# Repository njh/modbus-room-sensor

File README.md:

AL100 Modbus Room Sensor
========================

A temperature and humidity room sensor board for building automation. It is a Modbus RTU
server on RS-485, runs from 5–24 V DC, and fits in a standard wall-mounted room
sensor enclosure.

It uses a I²C sensor on a separate 19x19mm board, which is compatible with some of the
[Pimoroni Breakout Sensor Boards], so it is possible to use alternative sensors with it.

It is open source hardware and software: the KiCad design files, schematics,
Gerbers, bootloader and documentation are all MIT licensed, so you can build and
modify your own.

The board is Arduino compatible: it is designed to be very similar to the 3.3 V
[Arduino Pro Mini], so it can be programmed with the same settings.

Features
--------

- Sensirion [SHT4x] temperature and humidity sensor, on a swappable plug-in module
- Modbus RTU over half-duplex RS-485, with a ±70 V fault-protected transceiver
- Unit ID from 1 to 15, set with jumpers
- Jumper to enable the 120 Ω bus terminator
- 5–24 V DC supply, with a resettable fuse, reverse-polarity and surge protection
- Power and RS-485 on one 4-way HT396 connector, with the same pinout as M5Stack's [PWR485]
- Spare I²C socket for adding another sensor
- Fits the [Camdenboss CBRS01VWH] "Size 1" vented room sensor enclosure
- Designed in [KiCad], and assembled by JLCPCB

Downloads
---------

Schematics and Gerber files are built by GitHub Actions on every push to `main`,
and published as a [GitHub release][latest release]. These links always point to
the latest release:

| File                                       | Description                              |
|--------------------------------------------|------------------------------------------|
| [modbus-room-sensor-schematic.pdf]         | Main board schematic                     |
| [modbus-room-sensor-gerbers.zip]           | Main board Gerber and drill files        |
| [sht4x-breakout-schematic.pdf]             | SHT4x breakout board schematic           |
| [sht4x-breakout-gerbers.zip]               | SHT4x breakout board Gerber and drill files |

Specifications
--------------

| Item             | Value                                            |
|------------------|--------------------------------------------------|
| Supply voltage   | 5-24 V DC                                        |
| Interface        | RS-485, half-duplex                              |
| Protocol         | Modbus RTU, 9600 baud, 8N1                       |
| Unit ID          | 1-15, set by jumpers (default 1)                 |
| Sensor           | Sensirion SHT41: typically ±0.2 °C and ±1.8 %RH  |
| Resolution       | 0.1 °C and 0.1 %RH                               |
| Update interval  | 2 seconds                                        |
| Main board       | 73.3 x 73.3 mm, 2 layers                         |
| Enclosure        | [Camdenboss CBRS01VWH], 86 x 86 mm               |

Hardware
--------

### Main components

| Ref | Function             | Part                         |
|-----|----------------------|------------------------------|
| U1  | Microcontroller      | [ATmega328P] (3.3 V, 8 MHz)  |
| U3  | RS-485 transceiver   | [THVD2410]                   |
| U5  | 3.3 V buck converter | [AP63203]                    |
|     | Sensor               | [SHT4x], on the [SHT4x breakout board](sht4x-breakout/) |

### Connectors and jumpers

| Ref | Name         | Description |
|-----|--------------|-------------|
| J1  | Terminal     | 4-way 3.96 mm HT396 socket: `GND`, `VIN`, `A+`, `B-`. The same pinout as M5Stack's [PWR485], so it can share a 9–24 V supply and RS-485 bus with M5Stack devices |
| J2  | FTDI Serial  | 6-pin header for a 3.3 V FTDI cable, for uploading firmware and the debug console |
| J3  | ICSP         | 2x3 header for writing the bootloader |
| J4  | Sensor board | 5-way socket for the SHT4x breakout: `GND`, `INT`, `SCL`, `SDA`, `3.3V` |
| J5  | I2C          | 4-way JST PH socket: `SCL`, `SDA`, `3.3V`, `GND` (the same order as Grove and STEMMA) |
| J6  | Unit ID      | 2x4 header for the unit ID jumpers |
| JP1 | Terminate    | Fit a jumper to connect the 120 Ω terminator across A and B |

There are no I²C pull-up resistors on the main board. The SHT4x breakout has
4.7 kΩ pull-ups, so a sensor on J5 without the breakout needs its own.

Installation
------------

1. Set the unit ID by fitting jumpers on J6. The unit ID is the sum of the
   values printed next to the fitted jumpers (1, 2, 4 and 8), so fitting 1 and
   4 gives unit ID 5. With no jumpers fitted, the unit ID is 1. The jumpers are
   only read at power-up.
2. Connect the supply to `VIN` and `GND` on J1, and the RS-485 bus to `A+` and `B-`.
3. If the sensor is at one end of the bus, fit the `Terminate` jumper (JP1).
   Otherwise, leave it off.

Each device on the bus needs a unique unit ID.

Modbus Interface
----------------

The sensor board is a Modbus RTU server on RS-485 (J1), at 9600 baud, 8N1.

| Address  | Type                    | Name              | Format          | Units |
|----------|-------------------------|-------------------|-----------------|-------|
| `0x0001` | Input register (FC 04)  | Temperature       | Signed, x 10    | °C    |
| `0x0002` | Input register (FC 04)  | Relative humidity | Unsigned, x 10  | %RH   |

Addresses are the zero-based addresses sent on the bus. Tools that use
one-based 3xxxx numbering call these 30002 and 30003.

For example, `0x00EA` is 23.4 °C and `0xFFCB` is −5.3 °C. Both registers read
`0x8000` if the sensor couldn't be read.

### Reading the sensor

With a USB to RS-485 adapter, you can read the sensor using [modbus-cli]:

```sh
pip install modbus_cli
modbus -b 9600 -s 1 /dev/ttyUSB0 i@1/h i@2/H
```

Programming
-----------

The firmware is in [firmware/ModbusFirmware](firmware/ModbusFirmware). It needs
the [ModbusRTUSlave] and [Sensirion I2C SHT4x] libraries, which can be installed
with the Arduino IDE's Library Manager.

The board is programmed like a 3.3 V Arduino Pro Mini. In the Arduino IDE, choose
the **Arduino Pro or Pro Mini** board, with the **ATmega328P (3.3V, 8 MHz)**
processor option, and upload with a 3.3 V FTDI cable on J2.

A new board needs a bootloader before it can be programmed from the Arduino IDE.
See [bootloader/README.md](bootloader/README.md) for how to write it using ICSP.

Modbus doesn't work over the FTDI header, because the RS-485 receiver drives the
same RX line. Instead, at power-up the firmware prints when it was built, the unit
ID and the SHT4x serial number to the FTDI header, at 9600 baud.

ATmega328P pin mapping
----------------------

If you want to make your own software / firmware for the board, here is the
pin mapping for use in the Arduino IDE:

| Port | Arduino | Function                                |
|------|---------|-----------------------------------------|
| PD0  | D0      | UART RX, from RS-485 and FTDI           |
| PD1  | D1      | UART TX, to RS-485 and FTDI             |
| PD2  | D2      | RS-485 driver enable (DE)               |
| PD3  | D3      | RS-485 receiver enable (RE, active low) |
| PD4  | D4      | Sensor board interrupt                  |
| PD5  | D5      | _Unused_                                |
| PD6  | D6      | _Unused_                                |
| PD7  | D7      | _Unused_                                |
| PB0  | D8      | _Unused_                                |
| PB1  | D9      | _Unused_                                |
| PB2  | D10     | _Unused_                                |
| PB3  | D11     | ICSP MOSI                               |
| PB4  | D12     | ICSP MISO                               |
| PB5  | D13     | ICSP SCK and the Red LED                |
| PC0  | A0      | Unit ID jumper, value 1                 |
| PC1  | A1      | Unit ID jumper, value 2                 |
| PC2  | A2      | Unit ID jumper, value 4                 |
| PC3  | A3      | Unit ID jumper, value 8                 |
| PC4  | A4      | I²C data                                |
| PC5  | A5      | I²C clock                               |
| ADC6 | A6      | _Unused_                                |
| ADC7 | A7      | _Unused_                                |
| PC6  |         | Reset, from ICSP and FTDI auto-reset    |

Making a Board
--------------

The surface-mount parts are assembled by JLCPCB (Economic PCBA, top side only).
The LCSC part numbers are in the `LCSC` field of each part in the schematics.
In JLCPCB's placement preview, check the orientation of U1, U3, U5, D2 and D3.

The through-hole parts are fitted by hand. In soldering order:

| Ref | Part                                                    |
|-----|---------------------------------------------------------|
| J4  | 1x5 right-angle socket header, 2.54 mm                  |
| J5  | JST PH 4-way vertical socket (B4B-PH-K), optional       |
| F1  | Littelfuse RXEF050, 0.5 A resettable fuse               |
| J2  | 1x6 pin header, 2.54 mm                                 |
| J3  | 2x3 pin header, 2.54 mm                                 |
| J6  | 2x4 pin header, 2.54 mm, and jumpers                    |
| JP1 | 1x2 pin header, 2.54 mm, and a jumper                   |
| J1  | Kefa HT396R 4-way horizontal socket, 3.96 mm            |
| C1  | 47 µF 50 V electrolytic, 6.3 mm diameter, 2.5 mm pitch  |

You also need a [Camdenboss CBRS01VWH] enclosure, and 5 pan head M2.3 x 5 mm
self-tapping PCB screws.

License
-------

This project is open source hardware and software. The hardware design files,
software and documentation are all licensed under the terms of the MIT license.
See the file [LICENSE.md](LICENSE.md) for details.

[latest release]:  https://github.com/njh/modbus-room-sensor/releases/latest
[modbus-room-sensor-schematic.pdf]:  https://njh.github.io/modbus-room-sensor/modbus-room-sensor-schematic.pdf
[modbus-room-sensor-gerbers.zip]:    https://github.com/njh/modbus-room-sensor/releases/latest/download/modbus-room-sensor-gerbers.zip
[sht4x-breakout-schematic.pdf]:      https://njh.github.io/modbus-room-sensor/sht4x-breakout-schematic.pdf
[sht4x-breakout-gerbers.zip]:        https://github.com/njh/modbus-room-sensor/releases/latest/download/sht4x-breakout-gerbers.zip

[ATmega328P]:           https://www.microchip.com/en-us/product/atmega328p
[THVD2410]:             https://www.ti.com/product/THVD2410
[AP63203]:              https://www.diodes.com/part/view/AP63203
[SHT4x]:                https://sensirion.com/products/catalog/humidity-sensors?series=SHT4x
[KiCad]:                https://www.kicad.org/
[modbus-cli]:           https://github.com/favalex/modbus-cli
[ModbusRTUSlave]:       https://github.com/CMB27/ModbusRTUSlave
[Sensirion I2C SHT4x]:  https://github.com/Sensirion/arduino-i2c-sht4x

[Arduino Pro Mini]:                https://docs.arduino.cc/retired/boards/arduino-pro-mini/
[Camdenboss CBRS01VWH]:            https://www.camdenboss.com/ucommerce/cbrs01vwh-room-sensor-enclosure%2c-size-1%2c-vented%2c-white%2c-86x86x25.5mm/c-23/p-23038
[Pimoroni Breakout Sensor Boards]: https://shop.pimoroni.com/collections/breakouts?category=Sensors
[HT396]:                           https://www.kefaelectronic.com/HT396R-3-96-Pluggable-terminal-block-pd40161364.html
[PWR485]:                          https://docs.m5stack.com/en/stamp/Stamp_PWR485

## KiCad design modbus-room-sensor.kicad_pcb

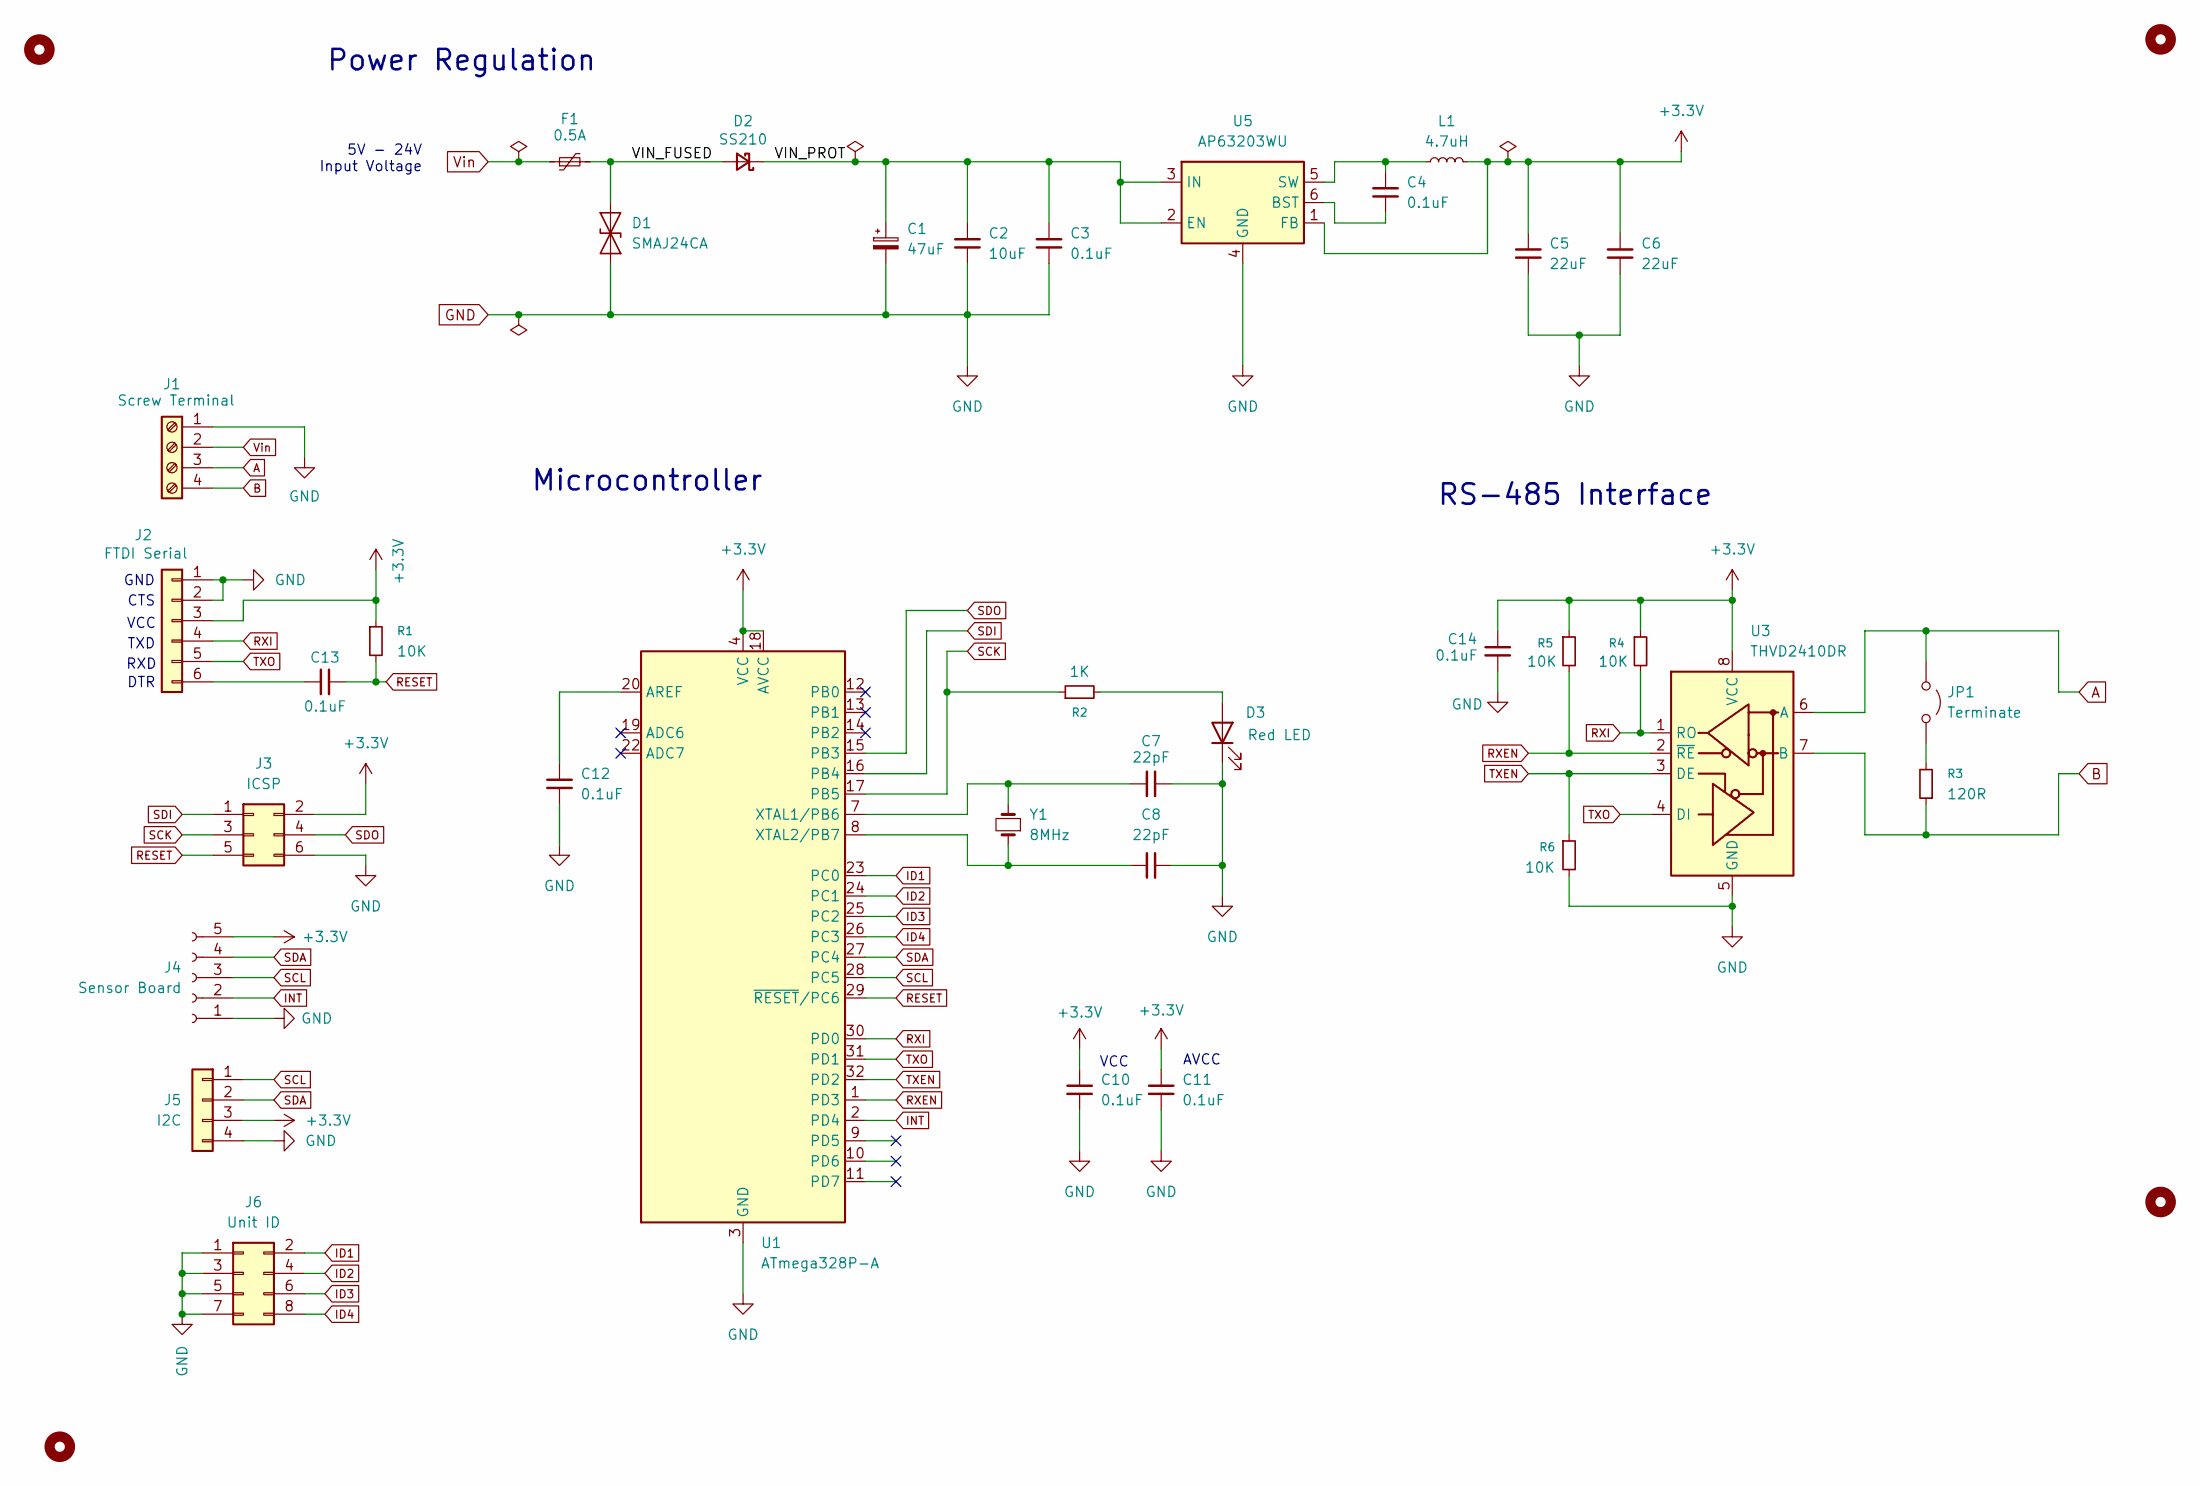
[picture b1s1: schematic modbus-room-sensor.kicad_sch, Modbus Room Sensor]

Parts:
C1: 47uF; CP_Radial_D6.3mm_P2.50mm
C2: 10uF; C_0805_2012Metric; LCSC C440198
C3, C4: 0.1uF; C_0603_1608Metric; LCSC C14663
C5, C6: 22uF; C_1206_3216Metric; LCSC C12891
C7, C8: 22pF; C_0603_1608Metric; LCSC C1653
C10, C11, C12, C13, C14: 0.1uF; C_0402_1005Metric; LCSC C1525
D1: SMAJ24CA; D_SMA; LCSC C19077542
D2: SS210; D_SMA; LCSC C14996
D3: Red LED; LED_0805_2012Metric; LCSC C84256
F1: 0.5A; C_Disc_D8.0mm_W5.0mm_P5.00mm
H1, H2, H3, H4: MountingHole; MountingHole_2.7mm_M2.5
J1: Screw Terminal; Kefa_HT396R-3.96-04P_1x04_P3.96mm_Horizontal
J2: FTDI Serial; PinHeader_1x06_P2.54mm_Vertical
J3: ICSP; PinHeader_2x03_P2.54mm_Vertical
J4: Sensor Board; PinSocket_1x05_P2.54mm_Horizontal
J5: I2C; JST_PH_B4B-PH-K_1x04_P2.00mm_Vertical
J6: Unit ID; PinHeader_2x04_P2.54mm_Vertical
JP1: Terminate; PinHeader_1x02_P2.54mm_Vertical
L1: 4.7uH; L_Sunlord_SWPA4030S; LCSC C57269
R1, R4, R5, R6: 10K; R_0603_1608Metric; LCSC C25804
R2: 1K; R_0603_1608Metric; LCSC C21190
R3: 120R; R_1206_3216Metric; LCSC C17909
U1: ATmega328P-A; TQFP-32_7x7mm_P0.8mm; LCSC C14877
U3: THVD2410DR; SOIC-8_3.9x4.9mm_P1.27mm; LCSC C1849398
U5: AP63203WU; TSOT-23-6; LCSC C780769
Y1: 8MHz; Crystal_SMD_5032-2Pin_5.0x3.2mm; LCSC C115962

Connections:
+3.3V: C5.1, C6.1, C10.1, C11.1, C14.1, J2.3, J3.2, J4.5, J5.3, L1.2, R1.1, R4.1, R5.1, U1.4 (VCC), U1.6 (VCC), U1.18 (AVCC), U3.8 (VCC), U5.1 (FB)
/VIN_FUSED: D1.2 (A2), D2.2 (A), F1.2
/VIN_PROT: C1.1, C2.1, C3.1, D2.1 (K), U5.2 (EN), U5.3 (IN)
A: J1.3, JP1.1 (A), U3.6 (A)
B: J1.4, R3.1, U3.7 (B)
GND: C1.2, C2.2, C3.2, C5.2, C6.2, C7.2, C8.2, C10.2, C11.2, C12.2, C14.2, D1.1 (A1), D3.1 (K), J1.1, J2.1, J2.2, J3.6, J4.1, J5.4, J6.1, J6.3, J6.5, J6.7, R6.2, U1.3 (GND), U1.5 (GND), U1.21 (GND), U3.5 (GND), U5.4 (GND)
ID1: J6.2, U1.23 (PC0)
ID2: J6.4, U1.24 (PC1)
ID3: J6.6, U1.25 (PC2)
ID4: J6.8, U1.26 (PC3)
INT: J4.2, U1.2 (PD4)
unnamed: D3.2 (A), R2.2
unnamed: C13.1, J2.6
unnamed: JP1.2 (B), R3.2
unnamed: C12.1, U1.20 (AREF)
unnamed: C7.1, U1.7 (XTAL1/PB6), Y1.2
unnamed: C8.1, U1.8 (XTAL2/PB7), Y1.1
unnamed: C4.2, U5.6 (BST)
unnamed: C4.1, L1.1, U5.5 (SW)
RESET: C13.2, J3.5, R1.2, U1.29 (~RESET/PC6)
RXEN: R5.2, U1.1 (PD3), U3.2 (~RE)
RXI: J2.4, R4.2, U1.30 (PD0), U3.1 (RO)
SCK: J3.3, R2.1, U1.17 (PB5)
SCL: J4.3, J5.1, U1.28 (PC5)
SDA: J4.4, J5.2, U1.27 (PC4)
SDI: J3.1, U1.16 (PB4)
SDO: J3.4, U1.15 (PB3)
TXEN: R6.1, U1.32 (PD2), U3.3 (DE)
TXO: J2.5, U1.31 (PD1), U3.4 (DI)
Vin: F1.1, J1.2

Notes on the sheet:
AVCC
TXD
VCC
Microcontroller
5V - 24V Input Voltage
CTS
GND
Power Regulation
DTR
RS-485 Interface
RXD

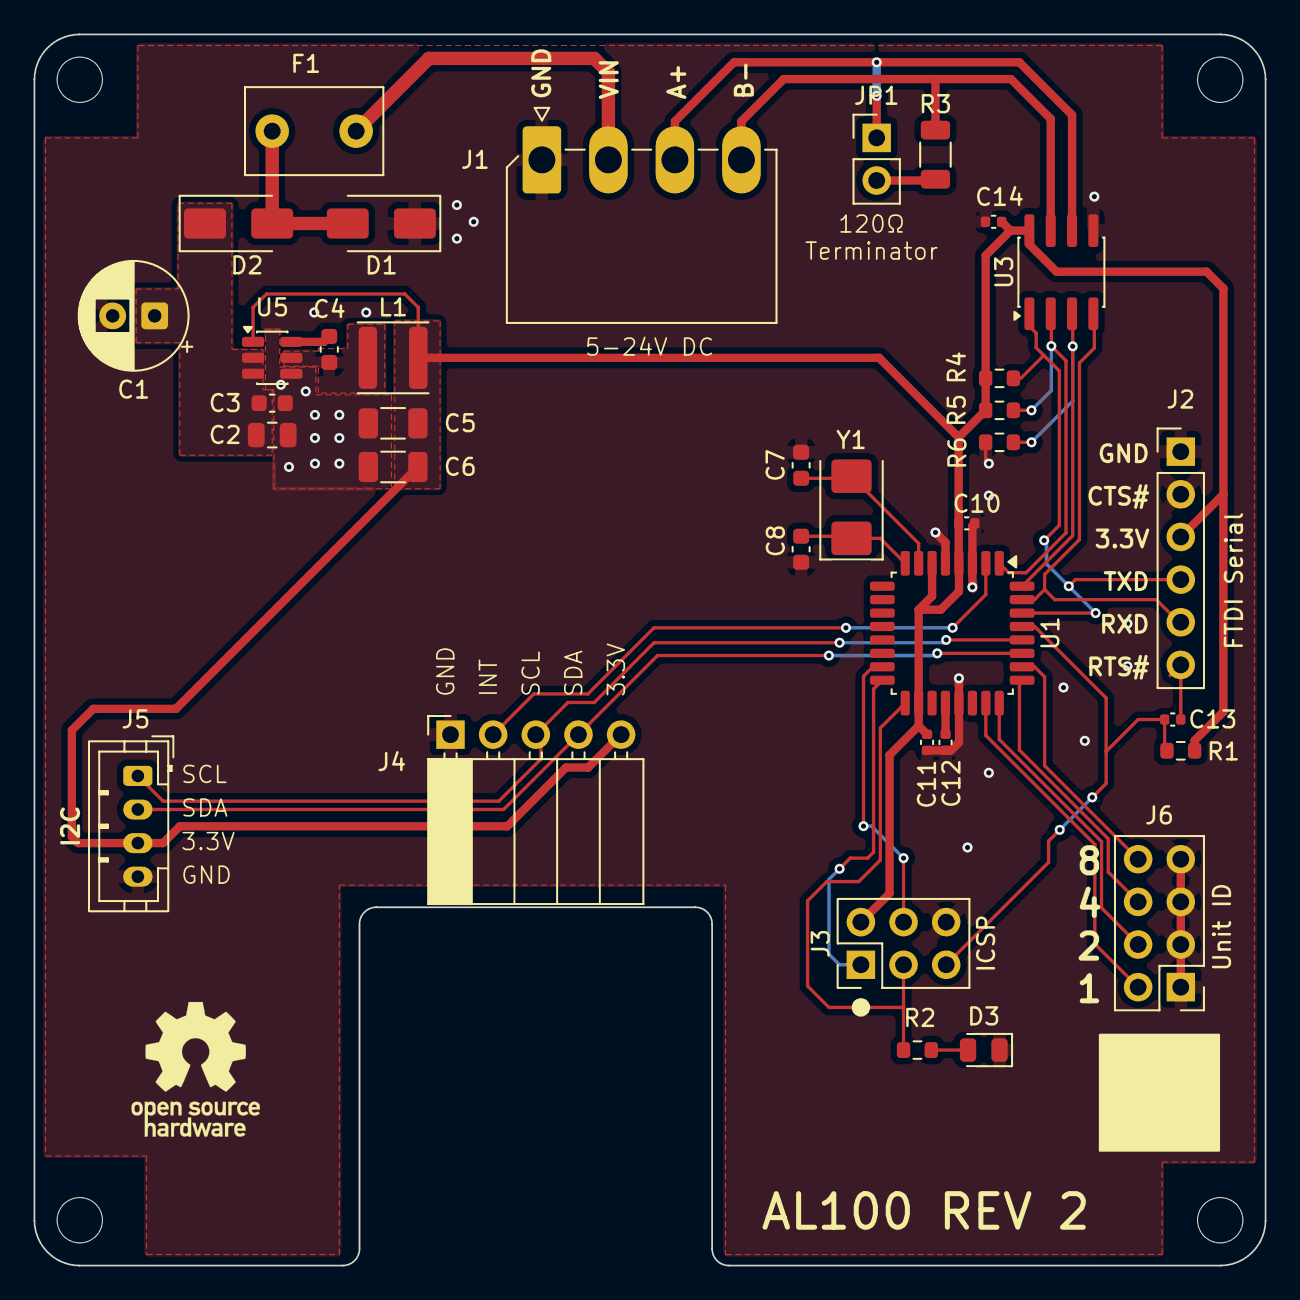
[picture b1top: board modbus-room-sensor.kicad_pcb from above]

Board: 2 copper layers, 73.3 x 73.3 mm, 39 parts (0 on the bottom side), 30 nets.

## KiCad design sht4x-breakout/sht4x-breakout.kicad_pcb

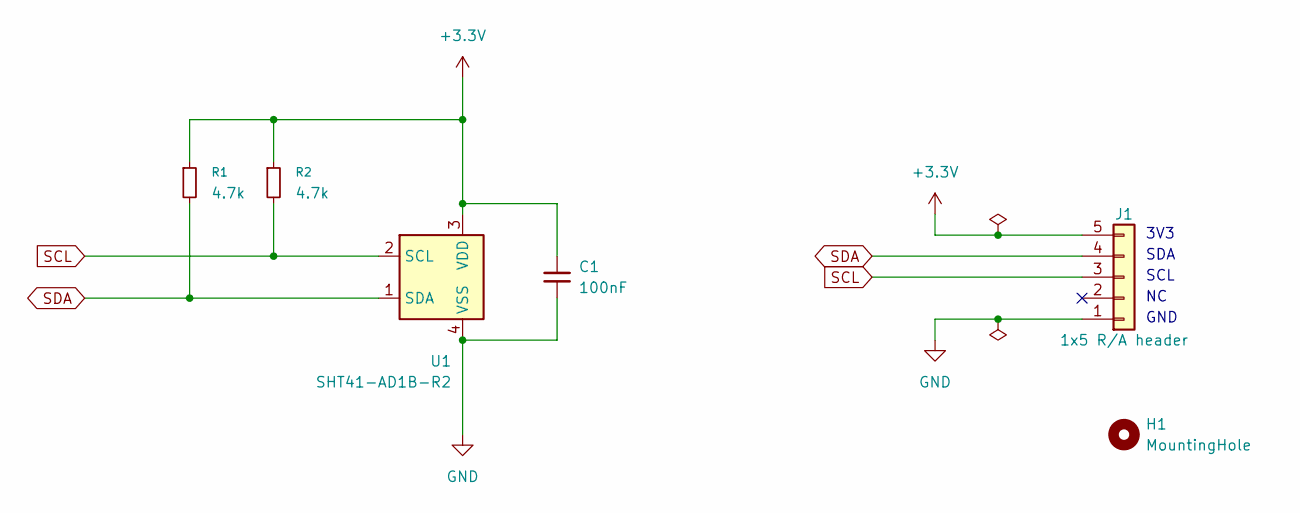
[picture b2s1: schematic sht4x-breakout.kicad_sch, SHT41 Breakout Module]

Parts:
C1: 100nF; C_0402_1005Metric; LCSC C1525
H1: MountingHole; MountingHole_2.7mm_M2.5
J1: 1x5 R/A header; PinHeader_1x05_P2.54mm_Vertical
R1, R2: 4.7k; R_0603_1608Metric; LCSC C23162
U1: SHT41-AD1B-R2; Sensirion_DFN-4_1.5x1.5mm_P0.8mm_SHT4x_NoCentralPad; LCSC C7461861

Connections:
+3.3V: C1.1, J1.5, R1.1, R2.1, U1.3 (VDD)
GND: C1.2, J1.1, U1.4 (VSS)
SCL: J1.3, R2.2, U1.2 (SCL)
SDA: J1.4, R1.2, U1.1 (SDA)

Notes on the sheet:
SCL
SDA
3V3
GND

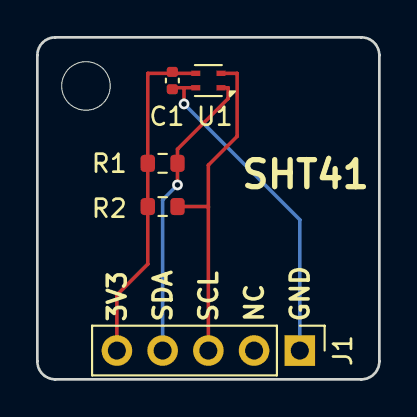
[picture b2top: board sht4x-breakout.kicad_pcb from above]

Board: 2 copper layers, 19.0 x 19.0 mm, 6 parts (0 on the bottom side), 4 nets.

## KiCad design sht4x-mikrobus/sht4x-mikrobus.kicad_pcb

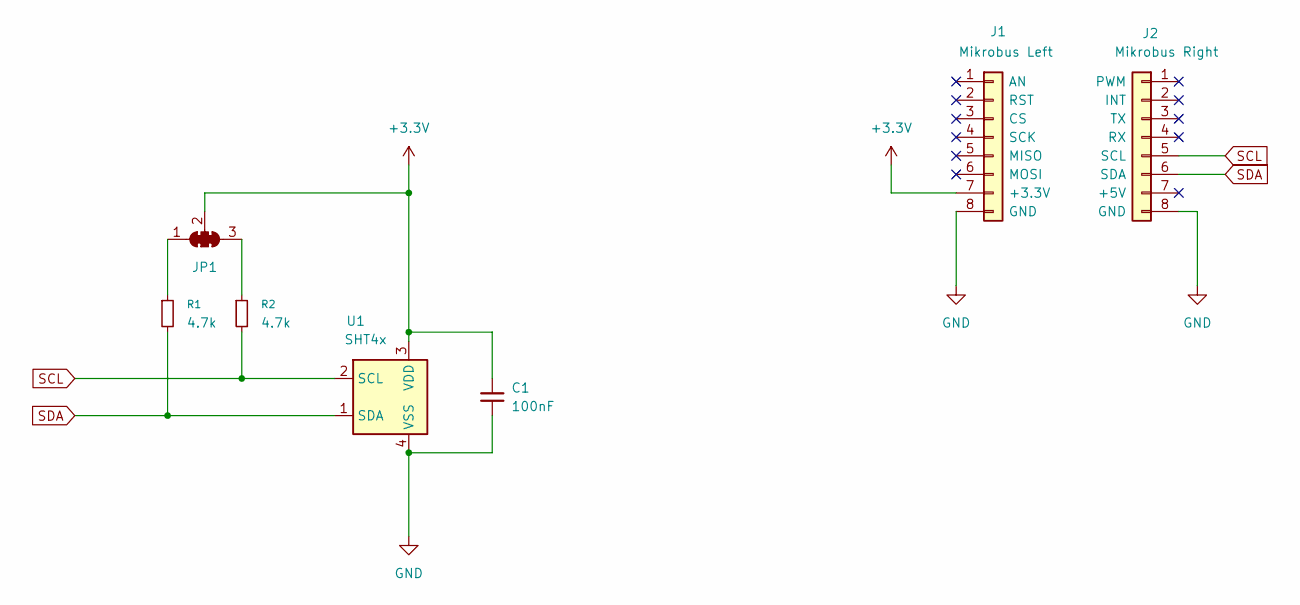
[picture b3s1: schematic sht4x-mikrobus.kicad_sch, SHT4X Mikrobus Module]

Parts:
C1: 100nF; C_0402_1005Metric; LCSC C1525
J1: Mikrobus Left; PinHeader_1x08_P2.54mm_Vertical
J2: Mikrobus Right; PinHeader_1x08_P2.54mm_Vertical
JP1: I2C Pullup; SolderJumper-3_P1.3mm_Bridged123_Pad1.0x1.5mm
R1, R2: 4.7k; R_0805_2012Metric; LCSC C17673
U1: SHT4x; Sensirion_DFN-4_1.5x1.5mm_P0.8mm_SHT4x_NoCentralPad; LCSC C5360602

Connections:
+3.3V: C1.1, J1.7 (+3.3V), JP1.2 (C), U1.3 (VDD)
GND: C1.2, J1.8 (GND), J2.8 (GND), U1.4 (VSS)
unnamed: JP1.1 (A), R1.1
unnamed: JP1.3 (B), R2.1
SCL: J2.5 (SCL), R2.2, U1.2 (SCL)
SDA: J2.6 (SDA), R1.2, U1.1 (SDA)

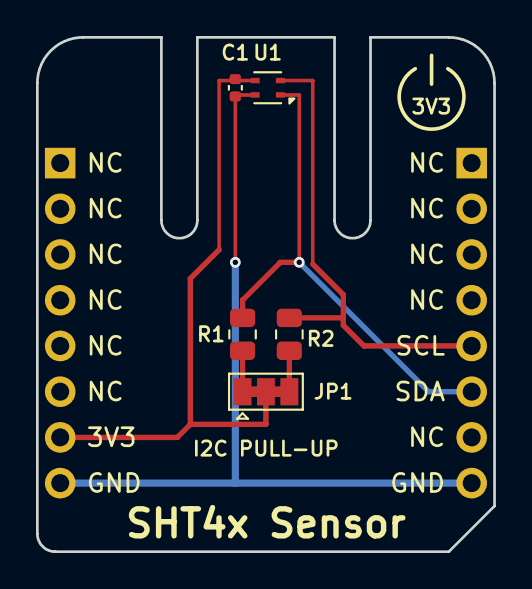
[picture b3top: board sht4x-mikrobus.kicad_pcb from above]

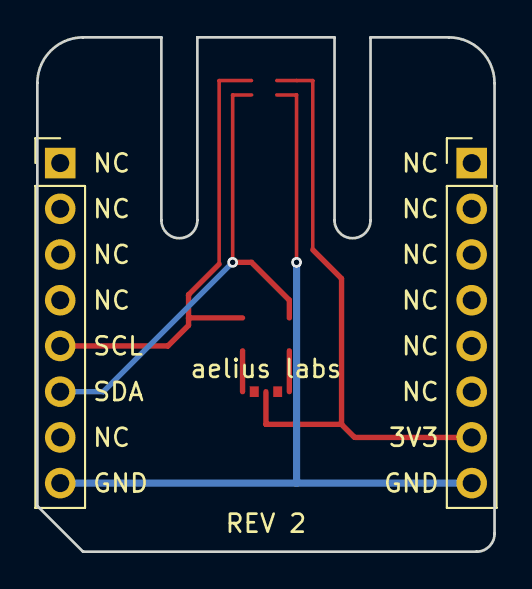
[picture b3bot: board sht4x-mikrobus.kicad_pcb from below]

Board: 2 copper layers, 25.4 x 28.6 mm, 7 parts (2 on the bottom side), 6 nets.

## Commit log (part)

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2025-05-19 Created empty KiCad project
2025-06-11 Added Evatron EN30 enclosure datasheet
2025-06-11 Added KiCAD .gitignore
2025-06-11 Schematic is close to being finished now.
2025-06-11 Created README
2025-06-12 MOSI → SDO, MISO → SDI https://oshwa.org/resources/a-resolution-to-redefine-spi-signal-names/
2025-06-12 Added MIT License
2026-02-08 Created PCB for SHT45 sensor on a MikroBus board
2026-02-08 Added jlcpcb to .gitignore (this contains generated production files)
2026-02-20 Switched to AP63203WU buck converter
2026-02-20 Make RXEN and TXEND indepentently controllable This is so we can disable RX during Optiboot

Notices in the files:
README.md:
License: MIT
